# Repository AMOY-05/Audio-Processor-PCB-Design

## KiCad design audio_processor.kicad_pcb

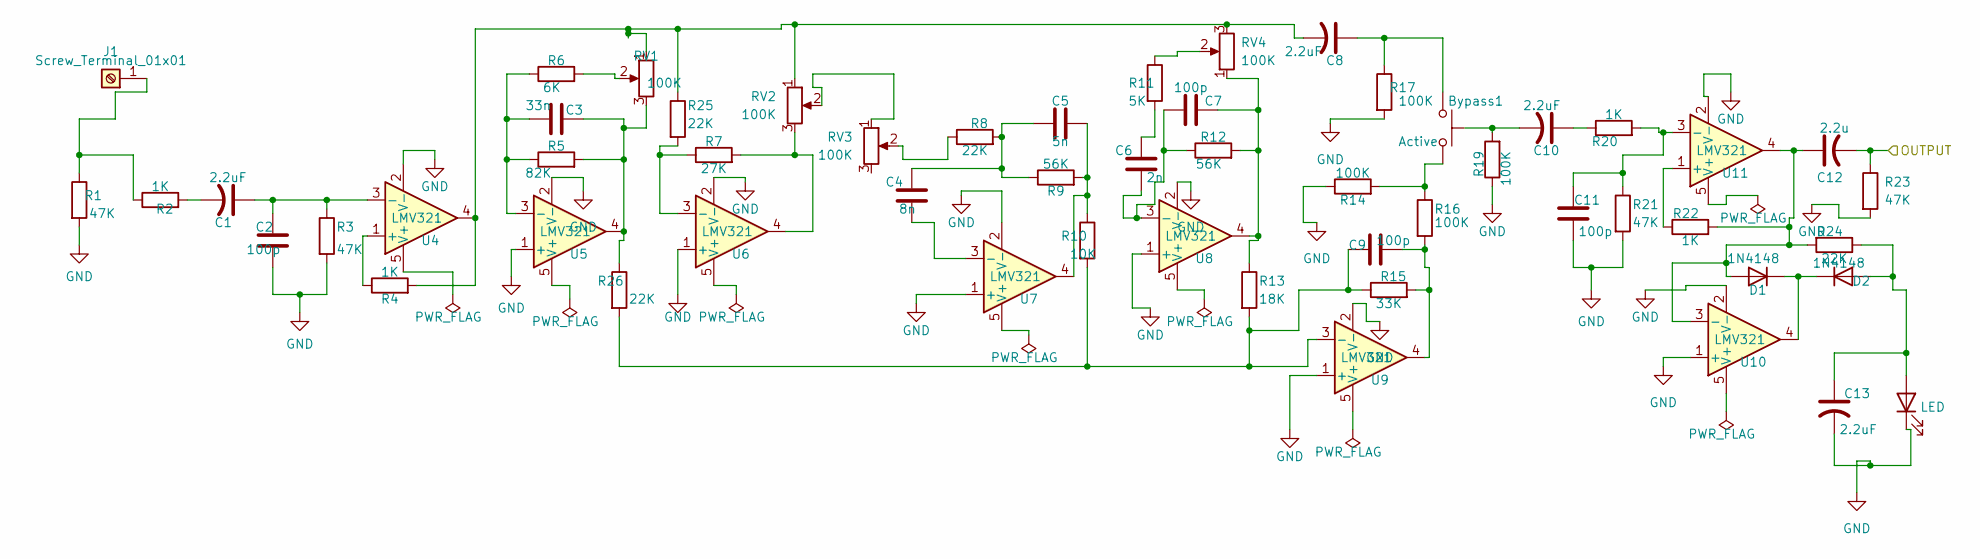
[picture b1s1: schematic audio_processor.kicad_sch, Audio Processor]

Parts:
Bypass1: Active; Nidec_Copal_CAS-120A
C1, C8, C10, C13: 2.2uF; CP_Radial_D12.5mm_P5.00mm
C2: 100p; CP_Axial_L25.0mm_D10.0mm_P30.00mm_Horizontal
C3: 33n; CP_Axial_L25.0mm_D10.0mm_P30.00mm_Horizontal
C4: 8n; CP_Axial_L42.0mm_D32.0mm_P45.00mm_Horizontal
C5: 5n; CP_Axial_L42.0mm_D32.0mm_P45.00mm_Horizontal
C6: 2n; CP_Radial_D40.0mm_P10.00mm_SnapIn
C7, C9, C11: 100p; CP_Axial_L38.0mm_D21.0mm_P44.00mm_Horizontal
C12: 2.2u; CP_Radial_D12.5mm_P5.00mm
D1, D2: 1N4148; D_DO-35_SOD27_P7.62mm_Horizontal
D3: LED; MagneticBuzzer_ProSignal_ABI-009-RC
J1: Screw_Terminal_01x01; SW_Push_SPST_NO_Alps_SKRK
R1, R21, R23: 47K; R_Axial_DIN0922_L20.0mm_D9.0mm_P25.40mm_Horizontal
R2, R20, R22: 1K; R_Axial_DIN0614_L14.3mm_D5.7mm_P25.40mm_Horizontal
R3: 47K; R_Axial_DIN0617_L17.0mm_D6.0mm_P20.32mm_Horizontal
R4: 1K; R_Axial_DIN0204_L3.6mm_D1.6mm_P7.62mm_Horizontal
R5: 82K; R_Axial_DIN0922_L20.0mm_D9.0mm_P25.40mm_Horizontal
R6: 6K; R_Axial_DIN0614_L14.3mm_D5.7mm_P25.40mm_Horizontal
R7: 27K; R_Axial_DIN0922_L20.0mm_D9.0mm_P25.40mm_Horizontal
R8, R24, R25, R26: 22K; R_Axial_DIN0922_L20.0mm_D9.0mm_P25.40mm_Horizontal
R9, R12: 56K; R_Axial_DIN0922_L20.0mm_D9.0mm_P25.40mm_Horizontal
R10: 10K; R_Axial_DIN0922_L20.0mm_D9.0mm_P25.40mm_Horizontal
R11: 5K; R_Axial_DIN0309_L9.0mm_D3.2mm_P20.32mm_Horizontal
R13: 18K; R_Axial_DIN0922_L20.0mm_D9.0mm_P25.40mm_Horizontal
R14: 100K; R_Axial_DIN0414_L11.9mm_D4.5mm_P20.32mm_Horizontal
R15: 33K; R_Axial_DIN0922_L20.0mm_D9.0mm_P25.40mm_Horizontal
R16, R17, R19: 100K; R_Axial_DIN0922_L20.0mm_D9.0mm_P30.48mm_Horizontal
RV1, RV2, RV3, RV4: 100K; Potentiometer_Bourns_3299Y_Vertical
U4, U5, U6, U7, U8, U9, U10, U11: LMV321; HTSOP-8-1EP_3.9x4.9mm_P1.27mm_EP2.4x3.2mm_ThermalVias

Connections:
/OUTPUT: C12.2, R23.1
GND: C2.2, C11.2, C13.2, D3.1 (K), R1.2, R3.2, R14.1, R17.2, R19.1, R21.2, R23.2, U4.2 (V-), U5.1 (+), U5.2 (V-), U6.1 (+), U6.2 (V-), U7.1 (+), U7.2 (V-), U8.1 (+), U8.2 (V-), U9.1 (+), U9.2 (V-), U10.1 (+), U10.2 (V-), U11.2 (V-)
unnamed: Bypass1.1, C8.1, R17.1
unnamed: Bypass1.2, R14.2, R16.1
unnamed: C1.2, R2.2
unnamed: C3.2, R5.2, R26.1, RV1.3, U5.4
unnamed: C4.1, C5.1, R8.2, R9.1
unnamed: C5.2, R9.2, R10.1, U7.4
unnamed: C6.1, R11.2
unnamed: C7.1, R12.2, R13.1, RV4.1, U8.4
unnamed: C8.2, R4.2, R25.1, RV1.1, RV2.1, RV4.3, U4.4
unnamed: C9.2, R15.2, R16.2, U9.4
unnamed: C10.1, R20.1
unnamed: C10.2, R19.2
unnamed: C12.1, D1.2 (A), R22.2, R24.2, U10.3 (-), U11.4
unnamed: D1.1 (K), D2.1 (K), U10.4
unnamed: C13.1, D2.2 (A), D3.2 (A), R24.1
unnamed: J1.1, R1.1, R2.1
unnamed: R6.2, RV1.2
unnamed: R7.2, RV2.3, U6.4
unnamed: R8.1, RV3.2
unnamed: R11.1, RV4.2
unnamed: RV2.2, RV3.1
unnamed: R4.1, U4.1 (+)
unnamed: C1.1, C2.1, R3.1, U4.3 (-)
unnamed: C3.1, R5.1, R6.1, U5.3 (-)
unnamed: R7.1, R25.2, U6.3 (-)
unnamed: C4.2, U7.3 (-)
unnamed: C6.2, C7.2, R12.1, U8.3 (-)
unnamed: C9.1, R10.2, R13.2, R15.1, R26.2, U9.3 (-)
unnamed: R22.1, U11.1 (+)
unnamed: C11.1, R20.2, R21.1, U11.3 (-)

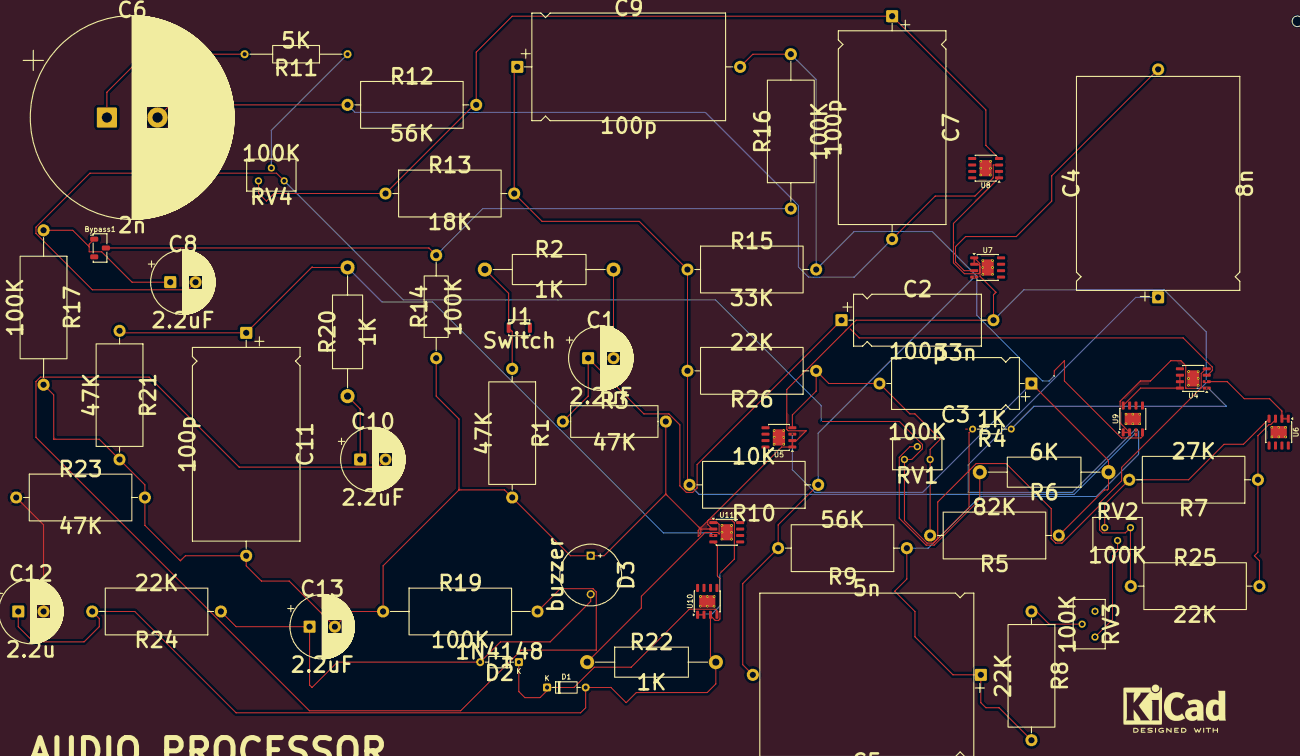
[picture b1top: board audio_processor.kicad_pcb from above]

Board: 2 copper layers, 55 parts (0 on the bottom side), 32 nets.
